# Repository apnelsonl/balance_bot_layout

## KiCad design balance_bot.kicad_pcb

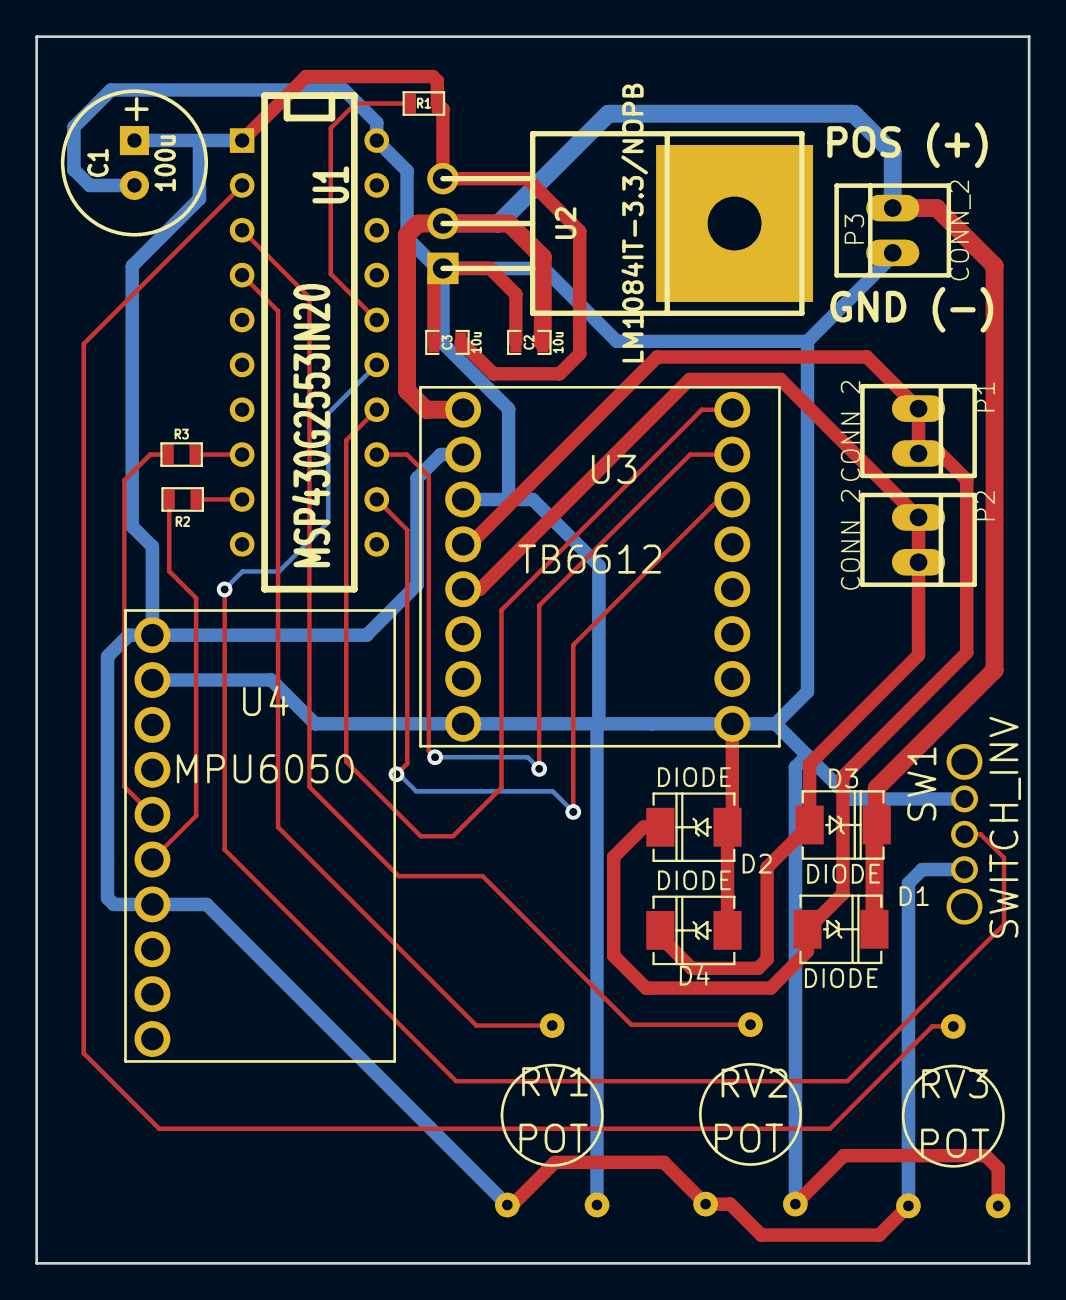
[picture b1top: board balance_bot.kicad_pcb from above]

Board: 2 copper layers, 56.2 x 69.4 mm, 21 parts (0 on the bottom side), 17 nets.

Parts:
C1: 100u; C1V8
C2, C3: 10u; SM0603_Capa
D1, D2, D3, D4: DIODE; DO-214AC(SMA)
P1, P2, P3: CONN_2; PINHEAD1-2
R1: 47k; SM0603
R2, R3: 2.2k; SM0603
RV1, RV2, RV3: POT; round_trimpot
SW1: SWITCH_INV; spdt
U1: MSP430G2553IN20; DIP-20__300
U2: LM1084IT-3.3/NOPB; TO220
U3: TB6612; tb6612
U4: MPU6050; mpu6050

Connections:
+7.4V: C2.1, D1.2, D3.2, P3.2, U2.3, U3.1
/VCC_MCU: C1.1, C3.1, R1.1, RV1.1, RV2.1, RV3.1, SW1.3, U1.1, U2.2, U3.2, U4.1, U4.7
GND: C1.2, C2.2, C3.2, D2.1, D4.1, P3.1, RV1.3, RV2.3, RV3.3, SW1.1, U1.20, U2.1, U3.3, U3.8, U3.9, U4.2
unnamed: D1.1, D2.2, P1.1, P1.2, U3.4
unnamed: D3.1, D4.2, P2.1, P2.2, U3.5
unnamed: R1.2, U1.16
unnamed: R3.1, U1.8
unnamed: R2.2, U4.6
unnamed: R3.2, U4.5
unnamed: RV3.2, U1.2
unnamed: RV2.2, U1.3
unnamed: RV1.2, U1.4
unnamed: R2.1, U1.9
unnamed: SW1.2, U1.15
unnamed: U1.14, U3.16
unnamed: U1.13, U3.15
unnamed: U1.12, U3.14

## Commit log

2013-11-19 Add KiCAD and gerber files
